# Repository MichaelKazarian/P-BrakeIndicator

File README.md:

# P-BrakeIndicator

**P-BrakeIndicator:** An ATtiny202-based automotive buzzer alert system to prevent driving with the handbrake engaged.

Компактний автомобільний пристрій контролю стоянкового гальма на мікроконтролері **ATtiny202** (серія tinyAVR 0). Система моніторить положення важеля ручника та активує звукове сповіщення у разі спроби руху з піднятим ручним гальмом, запобігаючи передчасному зносу гальмівної системи автомобіля.

---

## 🛠️ Апаратне забезпечення та інструменти

* **Мікроконтролер:** ATtiny202 (в корпусі SOIC-8).
* **Програматор:** USB-UART (TTL) адаптер на базі чіпа **QinHeng Electronics HL-340**.
* **Додатково:** Резистор **4.7 кОм** (або діод на кшталт 1N4148 / червоний світлодіод) для створення лінії SerialUPDI.

---

## 📊 Розпіновка та Специфікація (Pinout & Specification)

Для зручності монтажу та проектування нижче наведено схему розташування виводів мікроконтролера ATtiny202 (корпус SOIC-8) та його основні технічні характеристики:

---

## 🔌 Схема підключення (SerialUPDI)

Оскільки інтерфейс UPDI є однопровідним, лінії TX та RX адаптера HL-340 об'єднуються через резистор:

```text
USB-UART HL-340                       ATtiny202 (SOIC-8)
   [ TX ] -----[ Резистор 4.7 кОм ]-----+
                                        |
   [ RX ] ------------------------------+------> Pin 6 (PA0 / UPDI)

   [ GND ] ------------------------------------> Pin 8 (GND)
   [ 3.3V ] -----------------------------------> Pin 1 (VCC)
```
Для кращого розуміння фізичного монтажу ліній зв'язку нижче наведено візуальну схему:

⚠️ На цьому зображенні як апаратний міст показано плату Arduino. Проте **принцип об'єднання сигнальних ліній через резистор та підключення до чіпа повністю аналогічні нашому програматору** на базі USB-UART HL-340. Лінії передачі даних працюють за тією ж напівдуплексною логікою.

⚠️ **Важлива особливість для HL-340:** Адаптер видає логічні рівні 3.3 В. Для стабільної ініціалізації чіпа (щоб уникнути помилки `UPDI initialisation failed`), мікроконтролер ATtiny202 обов'язково має бути заживлений від **3.3 В**, а не від 5 В.

---

## 💻 Розробка за допомогою PlatformIO (Рекомендовано)

Для автоматизації збірки, керування життєвим циклом проєкту та комфортної роботи в текстових редакторах (наприклад, **Emacs**) використовується **PlatformIO Core**. 

Застарілий метод прошивки через `jtag2updi` більше **не працює**, тому конфігурація налаштована на пряме програмування через інтерфейс **SerialUPDI**.

### 1. Конфігурація `platformio.ini`
Рекомендованим способом ініціалізувати проект є виклик

``` shell
make init
```

або вручну

``` shell
platformio project init --ide emacs --board ATtiny202 \
--project-option "framework=arduino" \
--project-option "board_build.f_cpu=16000000L" \
--project-option "upload_protocol=serialupdi" \
--project-option "upload_speed=57600" \
# --project-option "upload_port=/dev/ttyUSB0"
# Автоматичне визначення або ручний вибір порту (за потреби розкоментуйте рядок вище)
```

Цей виклик згенерує структуру проекту і файл налаштувань `platformio.ini`. Додайте в кінець ці рядки:

``` ini
; Automatic detection or manual port selection (uncomment if needed)
; upload_port = /dev/ttyUSB0

[env:brake_indicator]
extends = env:ATtiny202
src_filter = +<brake_indicator.c> -<blink_test.c>

[env:blink_test]
extends = env:ATtiny202
src_filter = +<blink_test.c> -<brake_indicator.c>
```

Після ініціалізації проєкту файл налаштувань має містити параметри частоти, фіксованого порту та зниженої швидкості завантаження (`57600`), яка є критичною для стабільної роботи старого китайського чіпа HL-340 та профілі прошивки `brake_indicator` та `blink_test`:

```ini
[env:attiny202]
platform = atmelmegaavr
board = attiny202
framework = arduino
board_build.f_cpu = 16000000L
upload_protocol = serialupdi
upload_speed = 57600

; Automatic detection or manual port selection (uncomment if needed)
; upload_port = /dev/ttyUSB0

[env:brake_indicator]
extends = env:ATtiny202
src_filter = +<brake_indicator.c> -<blink_test.c>

[env:blink_test]
extends = env:ATtiny202
src_filter = +<blink_test.c> -<brake_indicator.c>
```

### 2. Керування проєктом через Makefile
Для швидкої збірки та прошивки безпосередньо з робочого оточення використовується дворівнева структура `Makefile`. Головний файл у корені проєкту автоматизує основні команди:

* `make init` — ініціалізує чистий проєкт для архітектури ATtiny202 з усіма необхідними параметрами прошивки та створює конфігурацію для Emacs.
* `make build` — компілює основний код програми (`brake_indicator.c`).
* `make upload` — прошиває мікроконтролер через підключений адаптер HL-340.
* `make upload-blink` — прошиває тестовий код блінка (`blink_test.c`) для перевірки заліза.
* `make clean` — очищає тимчасові файли збірки.
* `make monitor` — запускає монітор послідовного порту.

Внутрішній `src/Makefile` автоматично перенаправляє виклики на рівень вище за допомогою прапорця `-C ..`, що дозволяє запускати компіляцію чи прошивку прямо під час редагування файлу `src/main.cpp`.

## ⚙️  Альтернативне налаштування в Arduino IDE

1. Встановіть ядро **megaTinyCore** від SpenceKonde, додавши це посилання в менеджер плат:
   `https://github.com/SpenceKonde/megaTinyCore`
2. Перейдіть в **Інструменти** (Tools) та виберіть такі налаштування:
   * **Плата (Board):** megaTinyCore ➔ ATtiny202/402/212/412 (БЕЗ Optiboot!) *(Окремого пункту Bootloader немає, вибір інтегровано сюди)*
   * **Chip:** ATtiny202
   * **Clock:** 16 MHz internal
   * **Programmer:** `SerialUPDI - 57600 baud` *(Швидкість 57600 є критичною для стабільної роботи старого чіпа HL-340)*
   * **Port:** Ваш COM-порт (наприклад, `/dev/ttyUSB0` у Linux)

---

## 🚀 Як завантажити код

1. Підключіть тестовий світлодіод довгою ніжкою до **ніжки 2 (PA6)**, а короткою через резистор 220 Ом до **GND**.
2. Перевірте, що в меню вибору плат активовано саме варіант **(БЕЗ Optiboot!)**.
3. Натисніть стандартну кнопку **«Вантажити» (Upload)** в Arduino IDE. Програма автоматично викличе SerialUPDI та завантажить скетч.

---

## 📝 Тестовий скетч

У коді для PlatformIO обов'язково підключається заголовок `<Arduino.h>`, а піни задаються через системні константи. Для цього тесту світлодіод підключається до порту **PA3**, що фізично відповідає **ніжці 7** мікроконтролера ATtiny202.

Схема підключення світлодіода для перевірки працездатності:

### Код програми (`src/blink_test.c`)

```c
#include <Arduino.h>

// Для ATtiny202 в PlatformIO піни позначаються через PIN_PA6, PIN_PA7 тощо.
// Фізична ніжка 7 чіпа — це порт PA3.
const uint8_t LED_PIN = PIN_PA3; 

void setup() {
  pinMode(LED_PIN, OUTPUT);
}

void loop() {
  digitalWrite(LED_PIN, HIGH);
  delay(1000);
  digitalWrite(LED_PIN, LOW);
  delay(1000);
}
```

### Результат роботи

Після успішного завантаження програми світлодіод почне блимати з інтервалом в одну секунду, як показано на зображенні:

---

## 🔊 Схема підключення звукового випромінювача (2Т7000 MOSFET)

Для відтворення мелодії пасивний динамік або зумер підключається через N-канальний польовий транзистор **2N7000** за схемою Low-Side Switch. Для стабільної роботи без просідання живлення та захисту від перезавантаження мікроконтролера обов'язково використовуються обмежувальний, затворний та підтягуючий резистори:

* **Source (Витік / Ніжка 1 транзистора):** Підключається жорстко на **GND (Мінус / Маса)**.
* **Drain (Стік / Ніжка 3 транзистора):** Підключається до мінусового виводу динаміка.
* **Резистор 10 Ом (Gate Resistor):** Встановлюється у розрив лінії між виводом **PA3** та Затвором (Gate) для гасіння високочастотного дзвону та обмеження зарядного струму затвора.
* **Резистор 1 кОм (Pull-Down):** Встановлюється між Затвором (Gate) та Витоком (Source) для надійного закриття транзистора, коли мікроконтролер мовчить.
* **Резистор 100 Ом (Струмообмежувальний):** Підключається послідовно з динаміком у розрив ланцюга живлення **VCC (+3.3V / +5V)** для захисту лінії від імпульсних просідань напруги.

---

## 🔗 Корисні посилання
* [Посилання на специфікацію ATtiny202](https://ameblo.jp/pta55/entry-12784013578.html)
*Зверніть увагу: застарілий метод прошивки через `jtag2updi` більше **не працює** з новими версіями ядер, тому використовується пряме програмування через SerialUPDI.*
* [Детальна інструкція з налаштування середовища розробки ATtiny202 в Arduino IDE](https://burariweb.info)

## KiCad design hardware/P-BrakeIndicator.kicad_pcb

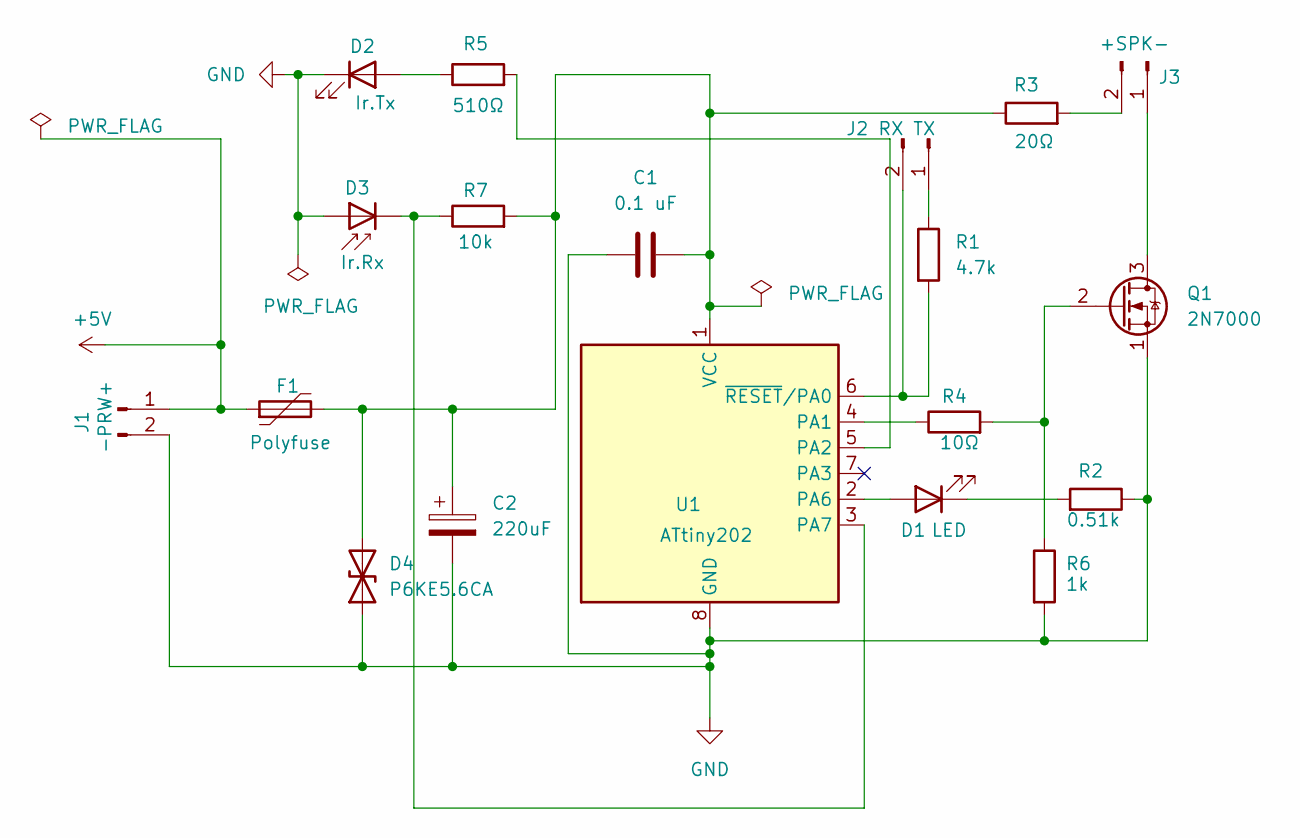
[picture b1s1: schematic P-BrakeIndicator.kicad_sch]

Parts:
C1: 0.1 uF; C_Disc_D5.0mm_W2.5mm_P5.00mm
C2: 220uF; CP_Radial_D5.0mm_P2.00mm
D1: LED; LED_D3.0mm
D2: Ir.Tx; LED_D3.0mm
D3: Ir.Rx; LED_D3.0mm
D4: P6KE5.6CA; D_T-1_P5.08mm_Horizontal
F1: Polyfuse; C_Disc_D5.0mm_W2.5mm_P5.00mm
J1: -PRW+; PinHeader_1x02_P2.54mm_Vertical
J2: RX TX; PinHeader_1x02_P2.54mm_Vertical
J3: +SPK-; PinHeader_1x02_P2.54mm_Vertical
Q1: 2N7000; TO-92_Inline
R1: 4.7k; R_Axial_DIN0207_L6.3mm_D2.5mm_P7.62mm_Horizontal
R2: 0.51k; R_Axial_DIN0207_L6.3mm_D2.5mm_P7.62mm_Horizontal
R3: 20Ω; R_Axial_DIN0207_L6.3mm_D2.5mm_P7.62mm_Horizontal
R4: 10Ω; R_Axial_DIN0207_L6.3mm_D2.5mm_P7.62mm_Horizontal
R5: 510Ω; R_Axial_DIN0207_L6.3mm_D2.5mm_P7.62mm_Horizontal
R6: 1k; R_Axial_DIN0207_L6.3mm_D2.5mm_P7.62mm_Horizontal
R7: 10k; R_Axial_DIN0207_L6.3mm_D2.5mm_P7.62mm_Horizontal
U1: ATtiny202; DIP-8_W7.62mm

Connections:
+5V: F1.1, J1.1
GND: C1.1, C2.2, D2.1 (K), D3.2 (A), D4.1 (A1), J1.2, Q1.1 (S), R2.1, R6.2, U1.8 (GND)
unnamed: D1.2 (A), U1.2 (PA6)
unnamed: D1.1 (K), R2.2
unnamed: D2.2 (A), R5.1
unnamed: D3.1 (K), R7.1, U1.3 (PA7)
unnamed: C1.2, C2.1, D4.2 (A2), F1.2, R3.1, R7.2, U1.1 (VCC)
unnamed: J2.1, R1.1
unnamed: J2.2, R1.2, U1.6 (~RESET/PA0)
unnamed: J3.1, Q1.3 (D)
unnamed: J3.2, R3.2
unnamed: Q1.2 (G), R4.2, R6.1
unnamed: R4.1, U1.4 (PA1)
unnamed: R5.2, U1.5 (PA2)

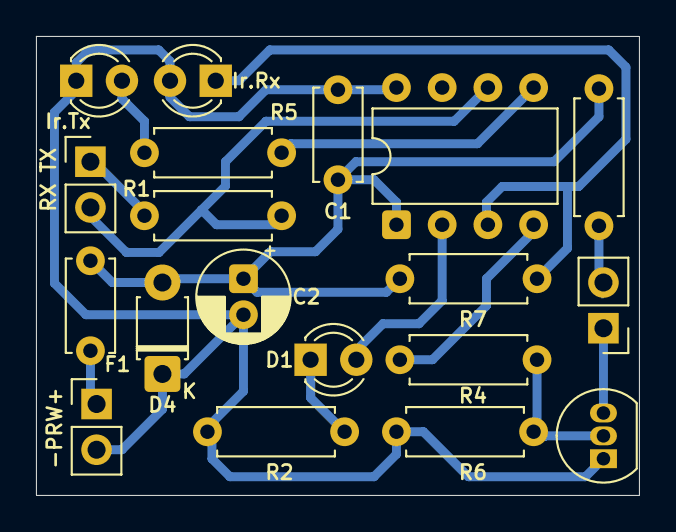
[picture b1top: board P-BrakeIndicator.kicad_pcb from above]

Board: 2 copper layers, 33.5 x 25.5 mm, 19 parts (0 on the bottom side), 14 nets.
